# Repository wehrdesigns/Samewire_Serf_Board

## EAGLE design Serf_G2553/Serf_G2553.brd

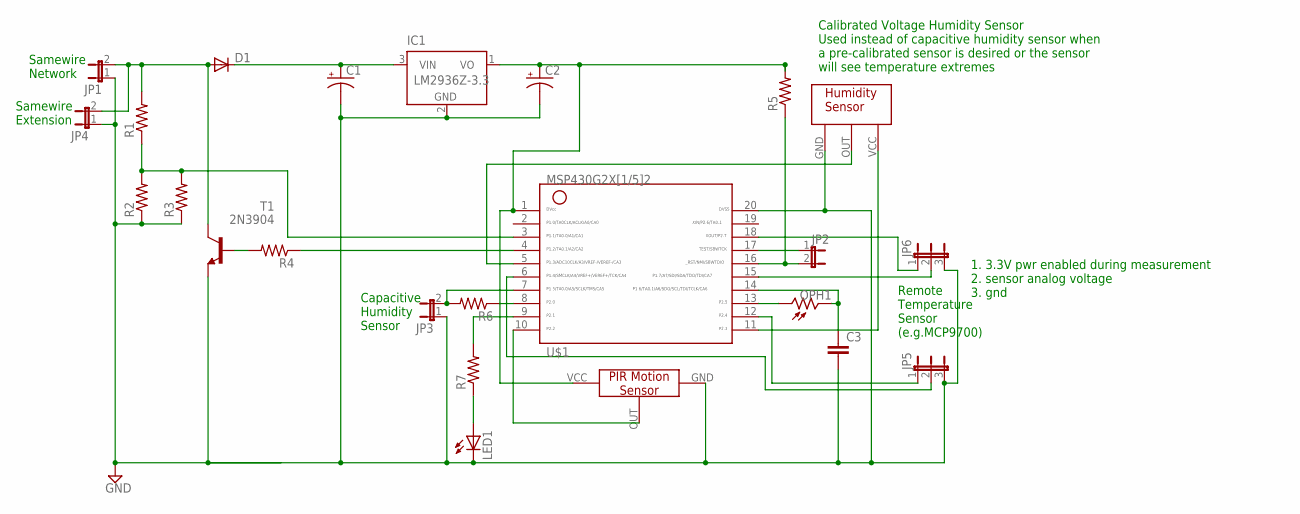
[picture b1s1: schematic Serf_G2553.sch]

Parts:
C1, C2: CPOL-USE2.5-6; E2,5-6
C3: C7.5/3; C7.5B3
D1: 1N4148DO35-7; DO35-7
IC1: LM2936Z-3.3; TO92
JP1, JP2, JP3, JP4: JP1E; JP1
JP5, JP6: JP2E; JP2
LED1: LED3MM
OPH1: VT90N1; VT900
R1, R2, R3, R4, R5, R6, R7: R-US_0204/2V; 0204V
T1: 2N3904; TO92
U$1: G2X[1/5]2---N20; N20
U$2: PANASONIC_PIR
U$3: HIH-5030; HIH-530

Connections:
GND: C1.-, C2.-, C3.2, IC1.2 (GND), JP1.1, JP3.1, JP4.1, JP5.3, JP6.3, LED1.K (C), R2.1, R3.1, T1.3 (E), U$1.20, U$2.GND, U$3.GND
unnamed: D1.A, JP1.2, JP4.2, R1.2, T1.1 (C)
unnamed: OPH1.1, U$1.13
unnamed: R4.1, U$1.4
unnamed: R1.1, R2.2, R3.2, U$1.3
unnamed: C3.1, OPH1.2, U$1.14
unnamed: R4.2, T1.2 (B)
unnamed: R6.1, U$1.8
unnamed: LED1.A, R7.1
unnamed: JP2.1, U$1.17
unnamed: R7.2, U$1.9
unnamed: JP3.2, R6.2, U$1.7
unnamed: U$1.10, U$2.OUT
unnamed: C1.+, D1.C, IC1.3 (VIN)
unnamed: C2.+, IC1.1 (VO), R5.2, U$1.1, U$2.VCC
unnamed: U$1.5, U$3.OUT
unnamed: U$1.11, U$3.VCC
unnamed: JP5.1, U$1.12
unnamed: JP5.2, U$1.6
unnamed: JP2.2, R5.1, U$1.16
unnamed: JP6.1, U$1.18
unnamed: JP6.2, U$1.15

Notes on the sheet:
Capacitive Humidity Sensor
Samewire Network
Samewire Extension
Remote Temperature Sensor (e.g.MCP9700)
1. 3.3V pwr enabled during measurement 2. sensor analog voltage 3. gnd
Calibrated Voltage Humidity Sensor Used instead of capacitive humidity sensor when a pre-calibrated sensor is desired or the sensor will see temperature extremes

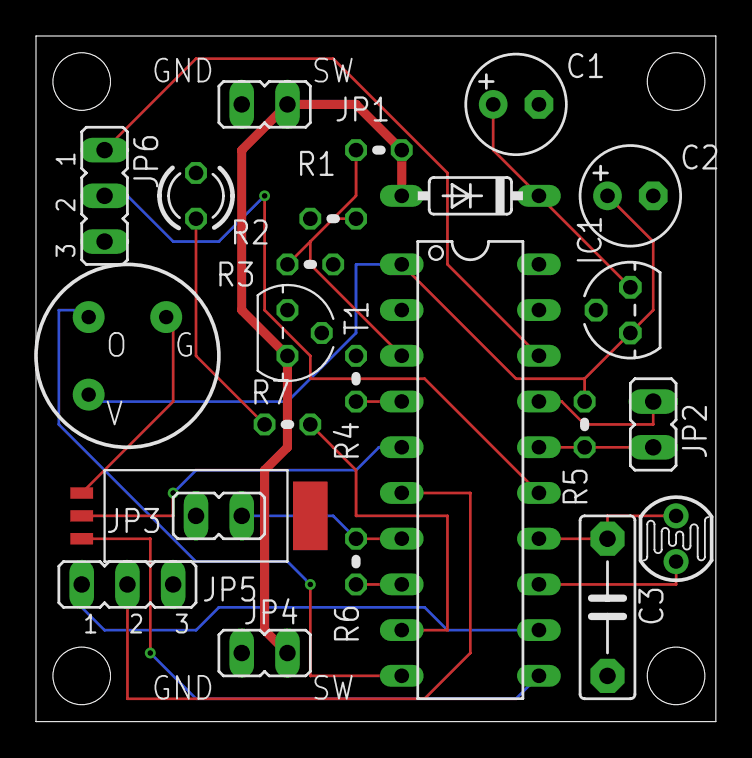
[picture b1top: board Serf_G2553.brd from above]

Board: 2 copper layers, 37.8 x 38.1 mm, 24 parts (0 on the bottom side), 22 nets.

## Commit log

2015-01-22 :octocat: Added .gitattributes & .gitignore files
2015-01-22 Upload Rev A
